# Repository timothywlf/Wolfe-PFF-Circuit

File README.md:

# Wolfe-PFF-Circuit
Documents for PFF

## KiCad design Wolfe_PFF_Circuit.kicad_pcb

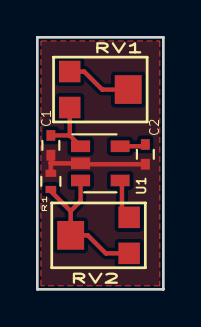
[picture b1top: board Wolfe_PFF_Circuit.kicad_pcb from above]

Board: 2 copper layers, 7.0 x 14.0 mm, 6 parts (0 on the bottom side), 6 nets.

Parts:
C1, C2: C_0402
R1: R_0402
RV1, RV2: Bourns_TrimPot_TC33_3mm
U1: SOT-23-5

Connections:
0-2V: RV1.1, RV1.2
+5V: C2.1, U1.5
GND: C1.2, C2.2, R1.2, U1.2
unnamed: C1.1, RV1.3, U1.1
unnamed: R1.1, RV2.1, RV2.2, U1.3
Output: RV2.3, U1.4
